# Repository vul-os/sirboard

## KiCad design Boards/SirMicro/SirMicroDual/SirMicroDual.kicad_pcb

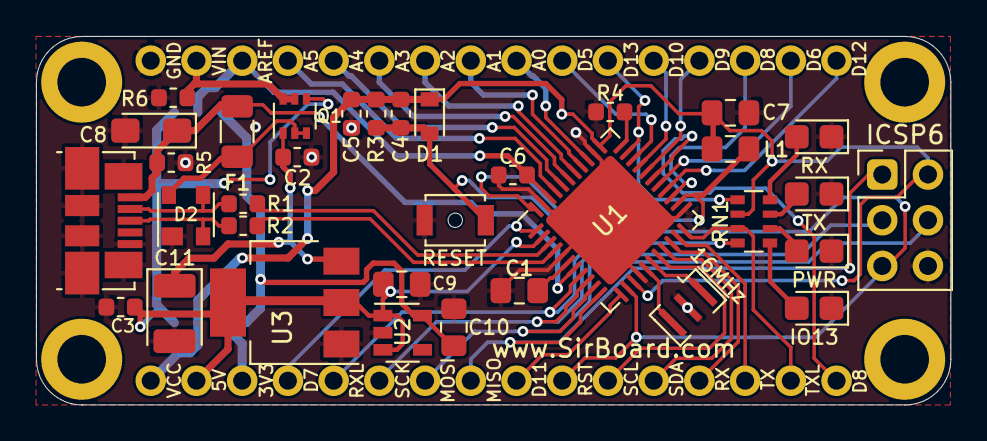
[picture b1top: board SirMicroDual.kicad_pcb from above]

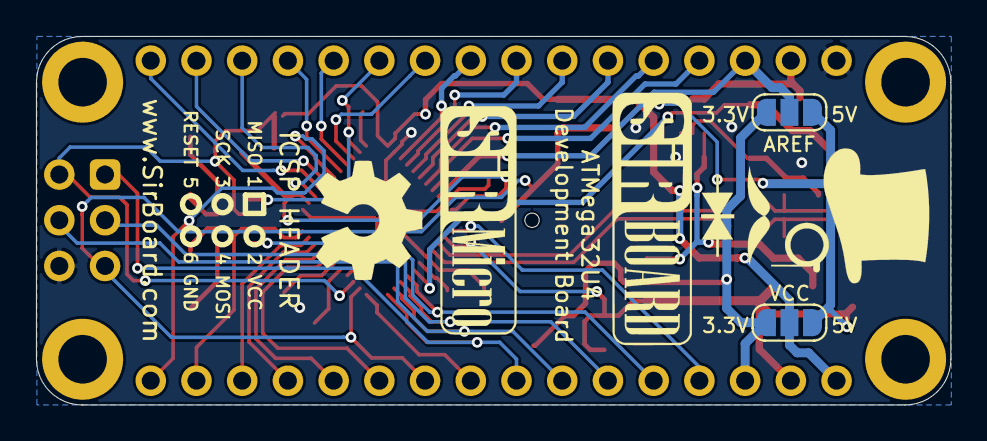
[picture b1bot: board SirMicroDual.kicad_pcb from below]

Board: 2 copper layers, 50.8 x 20.5 mm, 38 parts (4 on the bottom side), 48 nets.

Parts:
16MHz: 16MHz; Resonator_SMD_muRata_CSTxExxV-3Pin_3.0x1.1mm
C1, C7, C9, C10: 1uF; C_0805_2012Metric_Pad1.15x1.40mm_HandSolder
C2, C3, C4, C5, C6: 100nF; C_0603_1608Metric
C8: 22uF; CP_EIA-3216-18_Kemet-A_Pad1.58x1.35mm_HandSolder
C11: 22uF; CP_EIA-3528-12_Kemet-T
D1: D; D_SOD-110
D2: PRTR5V0U2X; SOT-143
F1: 500mA; R_1206_3216Metric
ICSP6: Conn_02x03_Odd_Even; PinHeader_2x03_P2.54mm_Vertical
IO13: LED; LED_0805_2012Metric_Castellated
J1, J2: Conn_01x16; PinHeader_1x16_P2.54mm_Vertical
J3: USB_B_Micro; USB_Micro-B_Molex_47346-0001
JP1, JP2: SolderJumper_3_Open; SolderJumper-3_P1.3mm_Open_RoundedPad1.0x1.5mm
L1: 10uH; L_0805_2012Metric_Pad1.15x1.40mm_HandSolder
PWR: LED; LED_0805_2012Metric_Castellated
Q1: DMP2004DWK-7; SOT-363_SC-70-6
R1, R2: 22e; R_0603_1608Metric
R3, R4, R5, R6: 10k; R_0603_1608Metric
RESET: SW_Push; SW_SPST_B3U-1000P-B
RN1: 1k; R_Array_Convex_4x0603
RX: LED; LED_0805_2012Metric_Castellated
TX: LED; LED_0805_2012Metric_Castellated
U1: ATmega32U4-MU; QFN-44-1EP_7x7mm_P0.5mm_EP5.2x5.2mm
U2: AP2127K-3.3; SOT-23-5
U3: AZ1117-5.0; SOT-223-3_TabPin2

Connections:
3V3: C10.1, J2.3, JP1.3, JP2.3, U2.5
5V: C3.1, C9.1, J2.2, JP1.1, JP2.1, Q1.4, U1.2, U2.1, U2.3, U3.2
/HWB: R4.1, U1.33
/X1: 16MHz.1, U1.17
/X2: 16MHz.3, U1.16
/uD+: R2.2, U1.4
/uD-: R1.2, U1.3
A0: J1.9, U1.36
A1: J1.8, U1.37
A2: J1.7, U1.38
A3: J1.6, U1.39
A4: J1.5, U1.40
A5: J1.4, U1.41
AREF: C6.1, J1.3, JP2.2, U1.42
D4: J1.14, U1.25
D5: J1.10, U1.31
D6: J1.15, U1.27
D7: J2.4, U1.1
D8: J2.16, U1.28
D9: J1.13, U1.29
D10: J1.12, U1.30
D11: J2.9, U1.12
D12: J1.16, U1.26
D13: J1.11, RN1.1, U1.32
D+: D2.2, J3.3, R2.1
D-: D2.3, J3.2, R1.1
GND: 16MHz.2, C1.2, C2.2, C3.2, C5.2, C6.2, C7.2, C8.2, C9.2, C10.2, C11.2, D2.1, ICSP6.6, IO13.1, J1.1, J3.5, J3.6, PWR.1, R4.2, R5.2, R6.2, RESET.1, RX.1, TX.1, U1.5, U1.15, U1.23, U1.35, U1.43, U1.45, U2.2, U3.1
MISO: ICSP6.1, J2.8, U1.11
MOSI: ICSP6.4, J2.7, U1.10
unnamed: C1.1, U1.6
unnamed: C8.1, F1.2, J3.1, R5.1, U1.7
unnamed: C2.1, C11.1, Q1.1, U3.3
unnamed: IO13.2, RN1.5
unnamed: L1.2, U1.24, U1.44
unnamed: PWR.2, RN1.6
unnamed: RN1.7, TX.2
unnamed: RN1.8, RX.2
RST: C4.2, D1.2, ICSP6.5, J2.10, R3.2, RESET.2, U1.13
RX: J2.13, U1.20
RXLED: J2.5, RN1.4, U1.8
SCK: ICSP6.3, J2.6, U1.9
SCL: J2.11, U1.18
SDA: J2.12, U1.19
TX: J2.14, U1.21
TXLED: J2.15, RN1.3, U1.22
VCC: C4.1, C5.1, C7.1, D1.1, ICSP6.2, J2.1, JP1.2, L1.1, R3.1, RN1.2, U1.14, U1.34
VIN: J1.2, Q1.5, Q1.6, R6.1
VUSB: D2.4, F1.1, Q1.2, Q1.3

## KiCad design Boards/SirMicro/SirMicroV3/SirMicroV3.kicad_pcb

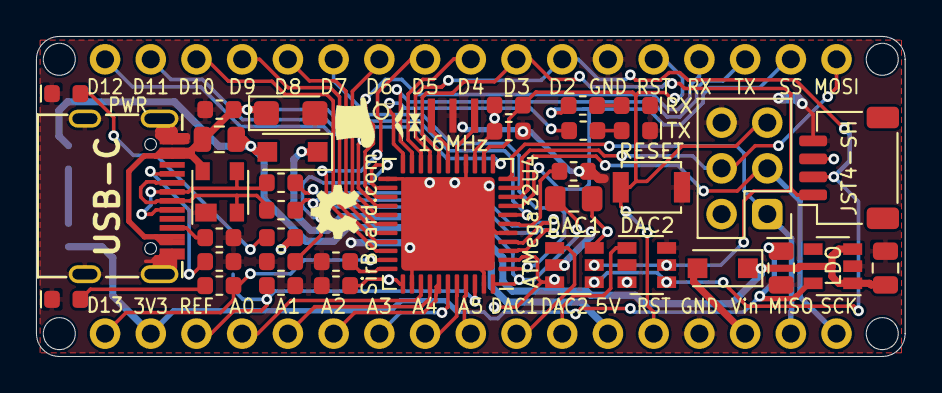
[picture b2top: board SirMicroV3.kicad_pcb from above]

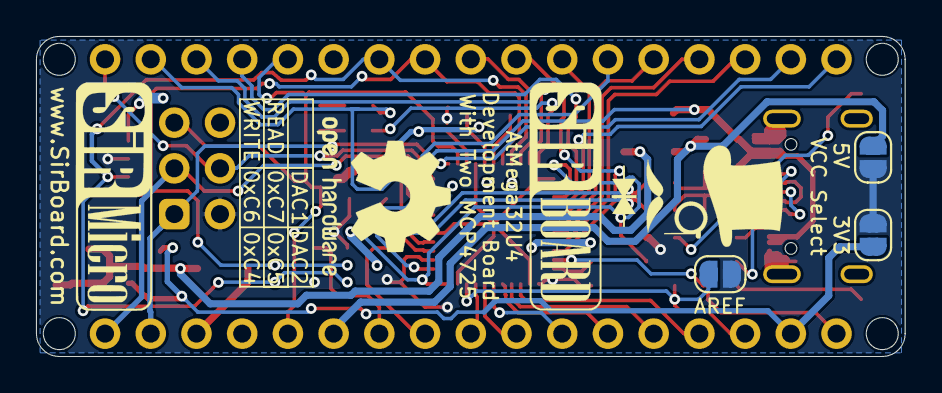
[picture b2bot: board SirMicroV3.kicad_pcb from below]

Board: 2 copper layers, 48.3 x 17.8 mm, 46 parts (5 on the bottom side), 51 nets.

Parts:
C1, C3, C4: 100nF; C_0603_1608Metric
C2, C9: 1uF; C_0603_1608Metric
C5, C7: 10uF; C_0805_2012Metric
C6: 10nF; C_0603_1608Metric
C8: 22uF; CP_EIA-3216-12_Kemet-S
D1: PRTR5V0U2X; SOT-143
D2, D3: MBR120; D_SOD-123F
D13: LED; LED_0603_1608Metric
DAC1, DAC2: MCP4725; SOT-23-6
F1: 500mA; R_0805_2012Metric
H1, H2, H3, H4: MountingHole; MountingHole_2.2mm_M2
J1, J2: Conn_01x17; PinHeader_1x17_P2.54mm_Vertical
J4: Conn_02x03_Odd_Even; PinHeader_2x03_P2.54mm_Vertical
JP1: AREF; SolderJumper-2_P1.3mm_Open_RoundedPad1.0x1.5mm
JP2, JP3: SolderJumper_2_Open; SolderJumper-2_P1.3mm_Open_RoundedPad1.0x1.5mm
JST4-SH: SirBlue; SirBlue_Connector
L1: 10uH; L_0805_2012Metric_Pad1.15x1.40mm_HandSolder
LDO: SPX3819M5-L-3-3; SOT-23-5
PWR: LED; LED_0603_1608Metric
R1, R2: 22e; R_0603_1608Metric
R3, R5: 10k; R_0603_1608Metric
R4, R8, R9, R10: 1k; R_0603_1608Metric
R11, R12: 5K1; R_0603_1608Metric
RESET: SW_Push; SW_SPST_B3U-1000P
RX: LED; LED_0603_1608Metric
TX: LED; LED_0603_1608Metric
U1: ATmega32U4-MU; QFN-44-1EP_7x7mm_P0.5mm_EP5.2x5.2mm
USB-C: USB_C_Plug_USB2.0; USB_C
Y1: 20MHz; Resonator_SMD_muRata_CSTxExxV-3Pin_3.0x1.1mm

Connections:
3V3: C7.1, J2.16, JP3.1, LDO.5
/D13LED: D13.2, R9.2
/HWB: R5.2, U1.33
/PWRLED: PWR.2, R10.2
/RXLED: R4.2, RX.2
/TXLED: R8.2, TX.2
/UCAP: C2.1, U1.6
/X1: U1.16, Y1.1
/X2: U1.17, Y1.3
A0: J2.14, U1.36
A1: J2.13, U1.37
A2: J2.12, U1.38
A3: J2.11, U1.39
A4: J2.10, U1.40
A5: J2.9, U1.41
AREF: C1.1, J2.15, JP1.2, U1.42
D4: J1.9, U1.20
D5: J1.10, U1.31
D6: J1.11, U1.27
D7: J1.12, U1.1
D8: J1.13, U1.28
D9: J1.14, U1.29
D10: J1.15, U1.30
D11: J1.16, U1.12
D12: J1.17, U1.26
D13: J2.17, R9.1, U1.32
D+: D1.3, R1.1, USB-C.A6, USB-C.B6
D-: D1.2, R2.1, USB-C.A7, USB-C.B7
GND: C1.2, C2.2, C3.2, C4.2, C5.2, C6.2, C7.2, C8.2, C9.2, D1.1, D13.1, DAC1.2, DAC2.2, DAC2.6, J1.6, J2.4, J4.6, JST4-SH.4, LDO.2, PWR.1, R5.1, R11.1, R12.1, RESET.2, RX.1, TX.1, U1.5, U1.15, U1.23, U1.35, U1.43, U1.45, USB-C.A1, USB-C.A12, USB-C.B1, USB-C.B12, USB-C.S1, Y1.2
MISO: J2.2, J4.1, U1.11
MOSI: J1.1, J4.4, U1.10
unnamed: C5.1, D2.1, D3.1, LDO.1, LDO.3
unnamed: C9.1, L1.2, U1.24, U1.44
unnamed: R12.2, USB-C.A5
unnamed: R11.2, USB-C.B5
RESET: J1.5, J2.5, J4.5, R3.2, RESET.1, U1.13
RX: J1.4, U1.25
RX_LED: J1.2, R4.1, U1.8
SCK: J2.1, J4.3, U1.9
SCL: DAC1.5, DAC2.5, J1.8, JST4-SH.1, U1.18
SDA: DAC1.4, DAC2.4, J1.7, JST4-SH.2, U1.19
TX: J1.3, U1.21
TX_LED: R8.1, U1.22
VBUS: C6.1, C8.1, D1.4, F1.2, U1.7, USB-C.A4, USB-C.A9, USB-C.B4, USB-C.B9
VCC: C3.1, C4.1, DAC1.3, DAC1.6, DAC2.3, J4.2, JP1.1, JP2.2, JP3.2, JST4-SH.3, L1.1, R3.1, R10.1, U1.2, U1.14, U1.34
VIN: D3.2, J2.3
VO1: DAC1.1, J2.8
VO2: DAC2.1, J2.7
VUSB: D2.2, F1.1, J2.6, JP2.1
uD+: R1.2, U1.4
uD-: R2.2, U1.3

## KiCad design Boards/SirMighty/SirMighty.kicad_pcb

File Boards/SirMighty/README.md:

# SirMighty
Microcontroller Development Board for the ATMega1284P which also works for the 644/324/32/16 derivatives. Fully Compatible with Arduino MightyCore

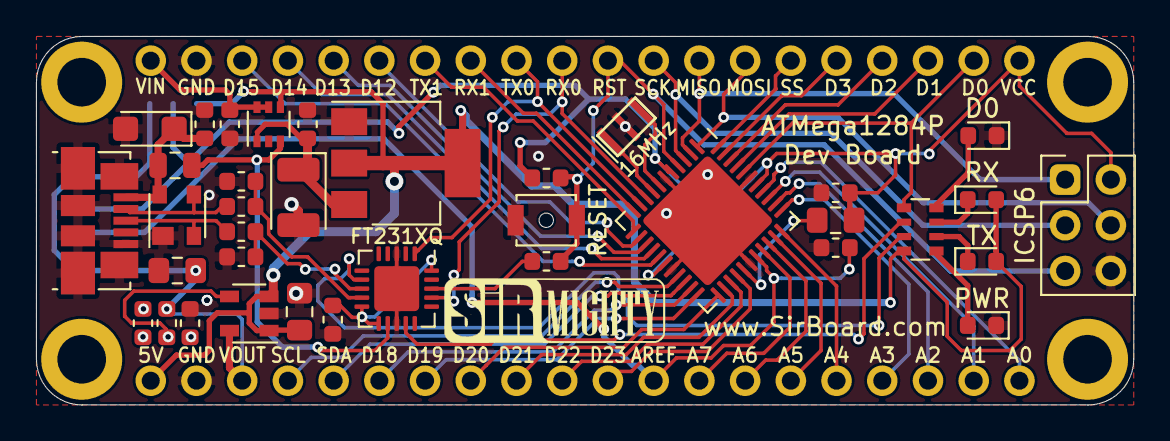
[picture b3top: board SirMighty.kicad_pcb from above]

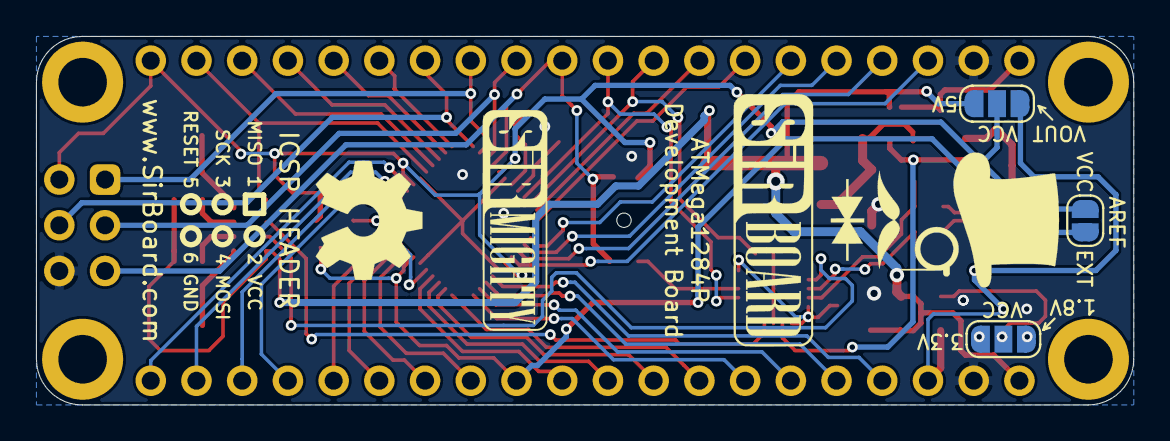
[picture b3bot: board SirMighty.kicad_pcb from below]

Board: 2 copper layers, 61.0 x 20.5 mm, 41 parts (5 on the bottom side), 60 nets.

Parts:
16MHz: 16MHz; Resonator_SMD_muRata_CSTxExxV-3Pin_3.0x1.1mm
C1, C5, C7, C11, C12: 100nF; C_0603_1608Metric
C2, C4: 47pF; C_0603_1608Metric
C3: 22uF; CP_EIA-3528-12_Kemet-T
C6: 10nF; C_0603_1608Metric
C8: 22uF; CP_EIA-3216-12_Kemet-S
C9, C10: 1uF; C_0805_2012Metric_Pad1.15x1.40mm_HandSolder
D0: LED; LED_0603_1608Metric
D1: PRTR5V0U2X; SOT-143
F1: 500mA; R_0805_2012Metric
FT231XQ: FT231XQ; QFN-20-1EP_4x4mm_P0.5mm_EP2.5x2.5mm
ICSP6: Conn_02x03_Odd_Even; PinHeader_2x03_P2.54mm_Vertical
J1, J2: Conn_01x20; PinHeader_1x20_P2.54mm_Vertical
J3: USB_B_Micro; USB_Micro-B_Molex_47346-0001
JP1: SolderJumper_2_Open; SolderJumper-2_P1.3mm_Open_RoundedPad1.0x1.5mm
JP2, JP3: SolderJumper_3_Open; SolderJumper-3_P1.3mm_Open_RoundedPad1.0x1.5mm
L1: 10uH; L_0805_2012Metric_Pad1.15x1.40mm_HandSolder
PWR: LED; LED_0603_1608Metric
Q1: Q_DUAL_PMOS_S1G1D2S2G2D1; SOT-363_SC-70-6
R1, R2: 27e; R_0603_1608Metric
R3, R4: 10k; R_0603_1608Metric
R5: 56k; R_0603_1608Metric
R6: 22k; R_0603_1608Metric
R7: 68k; R_0603_1608Metric
RESET: SW_Push; SW_SPST_B3U-1000P-B
RN1: 1k; R_Array_Convex_4x0603
RX: LED; LED_0603_1608Metric
TX: LED; LED_0603_1608Metric
U2: AP7365-W-7; SOT-23-5
U4: AZ1117-5.0; SOT-223-3_TabPin2
www.SirBoard.com: ATmega1284P-MU; QFN-44-1EP_7x7mm_P0.5mm_EP5.2x5.2mm

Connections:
3.3V: C12.2, FT231XQ.10, FT231XQ.11, FT231XQ.20
5V: C9.1, J1.1, JP3.3, Q1.4, RN1.4, RX.2, TX.2, U2.1, U2.3, U4.2
/D0LED: D0.2, RN1.8
/PWRLED: PWR.2, RN1.5
/X1: 16MHz.3, www.SirBoard.com.8
/X2: 16MHz.1, www.SirBoard.com.7
/uD+: C2.1, FT231XQ.8, R2.2
/uD-: C4.1, FT231XQ.9, R1.2
A0: J1.20, www.SirBoard.com.37
A1: J1.19, www.SirBoard.com.36
A2: J1.18, www.SirBoard.com.35
A3: J1.17, www.SirBoard.com.34
A4: J1.16, www.SirBoard.com.33
A5: J1.15, www.SirBoard.com.32
A6: J1.14, www.SirBoard.com.31
A7: J1.13, www.SirBoard.com.30
ADJ: JP2.2, R7.2, U2.4
AREF: C1.1, J1.12, JP1.1, www.SirBoard.com.29
D0: J2.19, RN1.1, www.SirBoard.com.40
D1: J2.18, www.SirBoard.com.41
D2: J2.17, www.SirBoard.com.42
D3: J2.16, www.SirBoard.com.43
D12: J2.6, www.SirBoard.com.13
D13: J2.5, www.SirBoard.com.14
D14: J2.4, www.SirBoard.com.15
D15: J2.3, www.SirBoard.com.16
D18: J1.6, www.SirBoard.com.21
D19: J1.7, www.SirBoard.com.22
D20: J1.8, www.SirBoard.com.23
D21: J1.9, www.SirBoard.com.24
D22: J1.10, www.SirBoard.com.25
D23: J1.11, www.SirBoard.com.26
D+: D1.2, J3.3, R2.1
D-: D1.3, J3.2, R1.1
GND: 16MHz.2, C1.2, C2.2, C3.2, C4.2, C5.2, C6.2, C7.2, C8.2, C9.2, C10.2, C12.1, D0.1, D1.1, FT231XQ.3, FT231XQ.13, FT231XQ.21, ICSP6.6, J1.2, J2.2, J3.5, J3.6, PWR.1, R4.2, R5.2, R6.2, RESET.2, U2.2, U4.1, www.SirBoard.com.6, www.SirBoard.com.18, www.SirBoard.com.28, www.SirBoard.com.39, www.SirBoard.com.45
MISO: ICSP6.1, J2.13, www.SirBoard.com.2
MOSI: ICSP6.4, J2.14, www.SirBoard.com.1
unnamed: C3.1, C5.1, Q1.1, U4.3
unnamed: C11.2, FT231XQ.18
unnamed: JP2.1, R6.1
unnamed: JP2.3, R5.1
unnamed: L1.2, www.SirBoard.com.27
unnamed: RN1.6, TX.1
unnamed: RN1.7, RX.1
RESET: C11.1, ICSP6.5, J2.11, R3.2, RESET.1, www.SirBoard.com.4
RXD0: FT231XQ.17, J2.10, www.SirBoard.com.9
RXD1: J2.8, www.SirBoard.com.11
RX_LED: FT231XQ.14, RN1.2
SCK: ICSP6.3, J2.12, www.SirBoard.com.3
SCL: J1.4, www.SirBoard.com.19
SDA: J1.5, www.SirBoard.com.20
SS: J2.15, www.SirBoard.com.44
TXD0: FT231XQ.1, J2.9, www.SirBoard.com.10
TXD1: J2.7, www.SirBoard.com.12
TX_LED: FT231XQ.7, RN1.3
VCC: C7.1, ICSP6.2, J2.20, JP1.2, JP3.2, L1.1, R3.1, www.SirBoard.com.5, www.SirBoard.com.17, www.SirBoard.com.38
VIN: J2.1, Q1.5, Q1.6, R4.1
VOUT: C10.1, J1.3, JP3.1, R7.1, U2.5
VUSB: F1.1, FT231XQ.12, Q1.2, Q1.3
Vbus: C6.1, C8.1, D1.4, F1.2, J3.1

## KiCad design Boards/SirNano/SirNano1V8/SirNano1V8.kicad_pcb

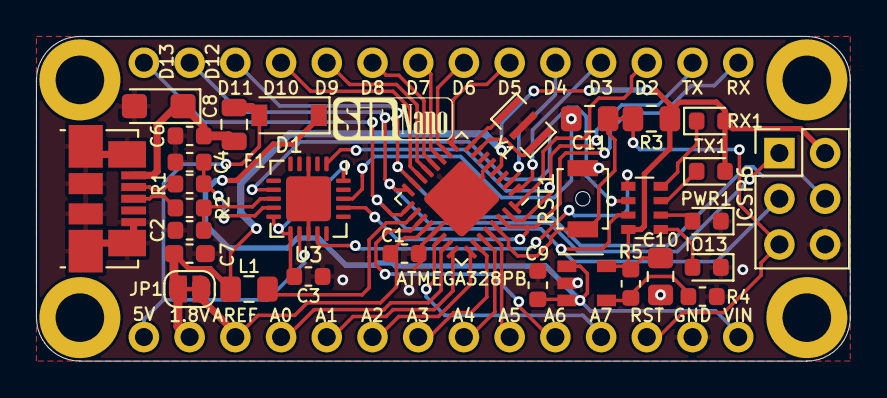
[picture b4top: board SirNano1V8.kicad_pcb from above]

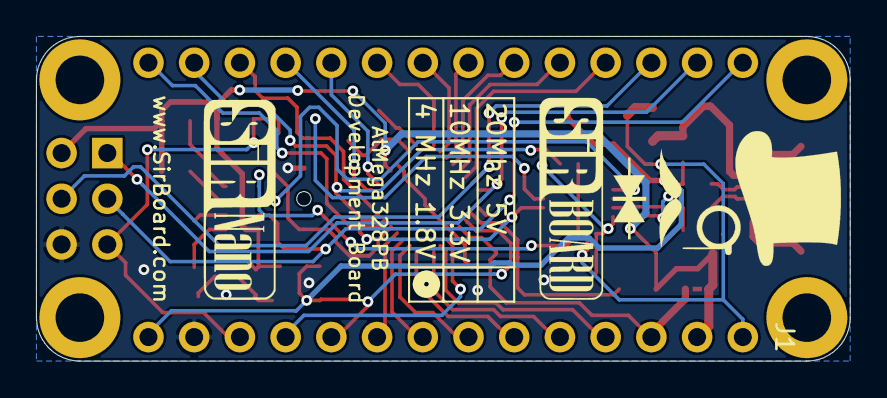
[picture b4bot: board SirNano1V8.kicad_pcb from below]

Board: 2 copper layers, 45.2 x 18.0 mm, 33 parts (2 on the bottom side), 45 nets.

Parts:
C1, C3: 100nF; C_0603_1608Metric
C2, C4: 47pF; C_0603_1608Metric
C6: 10nF; C_0603_1608Metric
C7: 1uF; C_0603_1608Metric_Pad1.05x0.95mm_HandSolder
C8: 22uF; CP_EIA-3216-12_Kemet-S
C9: 1uF; C_0603_1608Metric
C10: 2.2uF; C_0805_2012Metric_Pad1.15x1.40mm_HandSolder
C11: 100nF; C_0805_2012Metric_Pad1.15x1.40mm_HandSolder
D1: D_Schottky; D_SOD-123
F1: 500mA; R_0805_2012Metric
ICSP6: Conn_02x03_Odd_Even; PinHeader_2x03_P2.54mm_Vertical
IO13: LED; LED_0603_1608Metric
J1, J2: Conn_01x14; PinHeader_1x14_P2.54mm_Vertical
J3: USB_B_Micro; USB_Micro-B_Molex_47346-0001
JP1: SolderJumper_2_Bridged; SolderJumper-2_P1.3mm_Bridged_RoundedPad1.0x1.5mm
L1: 10uH; L_0805_2012Metric_Pad1.15x1.40mm_HandSolder
PWR1: LED; LED_0603_1608Metric
R1, R2: 27e; R_0603_1608Metric
R3: 10k; R_0805_2012Metric_Pad1.15x1.40mm_HandSolder
R4: 100k; R_0603_1608Metric
R5: 220k; R_0603_1608Metric
RN1: 1k; R_Array_Convex_4x0603
RST1: SW_Push; SW_SPST_B3U-1000P-B
RX1: LED; LED_0603_1608Metric
TX1: LED; LED_0603_1608Metric
U1: ATmega328PB-MU; QFN-32-1EP_5x5mm_P0.5mm_EP3.1x3.1mm
U2: AP2210K-ADJ; SOT-23-5
U3: FT231XQ; QFN-20-1EP_4x4mm_P0.5mm_EP2.5x2.5mm
Y1: 4MHz; Resonator_SMD_muRata_CSTxExxV-3Pin_3.0x1.1mm

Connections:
1V8: C7.1, C10.1, ICSP6.2, J1.2, JP1.2, L1.1, R3.1, R5.2, RN1.4, RX1.2, TX1.2, U1.4, U2.5
3V3: C3.1, U3.10, U3.11, U3.20
5V: D1.2, F1.1, J1.1, U3.12
/AREF: C1.1, J1.3, JP1.1, U1.20
/D2: J2.12, U1.32
/D3: J2.11, U1.1
/D4: J2.10, U1.2
/D5: J2.9, U1.9
/D6: J2.8, U1.10
/D7: J2.7, U1.11
/D8: J2.6, U1.12
/D9: J2.5, U1.13
/D10: J2.4, U1.14
/D+: J3.3, R2.1
/D-: J3.2, R1.1
/IO13LED: IO13.2, RN1.5
/PWRLED: PWR1.2, RN1.6
/RX: J2.14, U1.30, U3.17
/TX: J2.13, U1.31, U3.1
/X1: U1.7, Y1.3
/X2: U1.8, Y1.1
/uD+: C2.1, R2.2, U3.8
/uD-: C4.1, R1.2, U3.9
A0: J1.4, U1.23
A1: J1.5, U1.24
A2: J1.6, U1.25
A3: J1.7, U1.26
A4: J1.8, U1.27
A5: J1.9, U1.28
A6: J1.10, U1.19
A7: J1.11, U1.22
D11: ICSP6.4, J2.3, U1.15
D12: ICSP6.1, J2.2, U1.16
D13: ICSP6.3, J2.1, RN1.3, U1.17
GND: C1.2, C2.2, C3.2, C4.2, C6.2, C7.2, C8.2, C9.2, C10.2, ICSP6.6, IO13.1, J1.13, J3.5, J3.6, PWR1.1, R4.2, RST1.2, U1.5, U1.21, U1.33, U2.2, U3.3, U3.13, U3.21, Y1.2
unnamed: C6.1, C8.1, F1.2, J3.1
unnamed: C11.2, U3.18
unnamed: L1.2, U1.18
unnamed: R4.1, R5.1, U2.4
unnamed: RN1.7, TX1.1
unnamed: RN1.8, RX1.1
RESET: C11.1, ICSP6.5, J1.12, R3.2, RST1.1, U1.29
RX_LED: RN1.1, U3.14
TX_LED: RN1.2, U3.7
VIN: C9.1, D1.1, J1.14, U2.1, U2.3

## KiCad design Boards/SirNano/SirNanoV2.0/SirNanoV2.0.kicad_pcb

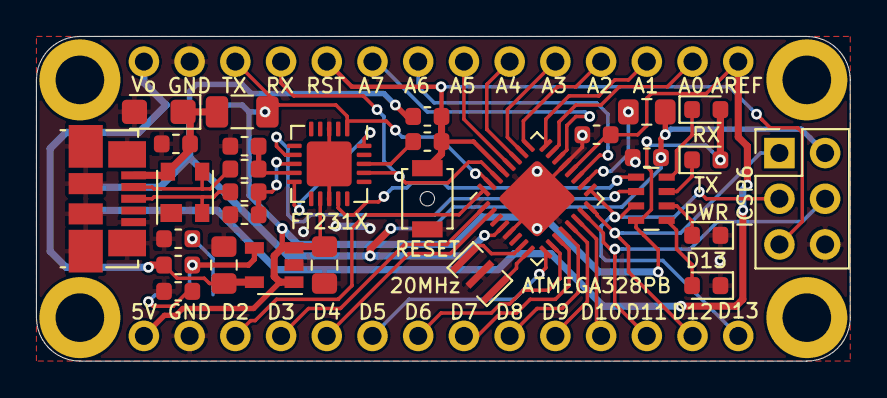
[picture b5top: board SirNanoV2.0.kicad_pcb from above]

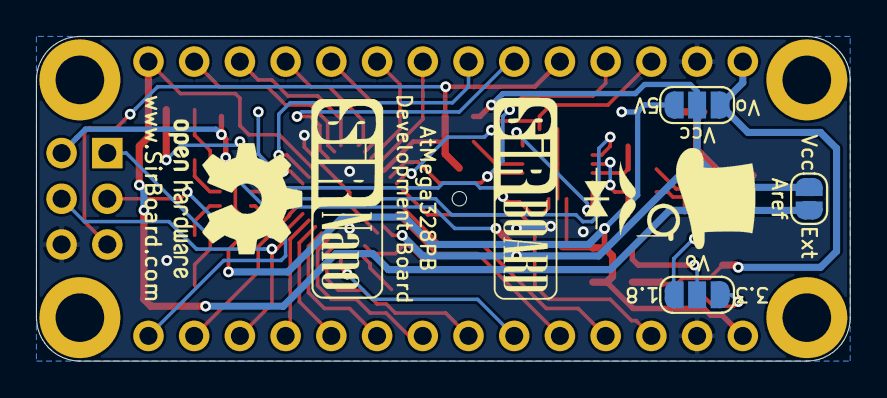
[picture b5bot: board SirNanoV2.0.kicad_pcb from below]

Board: 2 copper layers, 45.2 x 18.0 mm, 35 parts (5 on the bottom side), 47 nets.

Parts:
20MHz: 20MHz; Resonator_SMD_muRata_CSTxExxV-3Pin_3.0x1.1mm
C1, C11: 100nF; C_0603_1608Metric
C2, C4: 47pF; C_0603_1608Metric
C6: 10nF; C_0603_1608Metric
C7: 1uF; C_0603_1608Metric
C8: 22uF; CP_EIA-3216-12_Kemet-S
C9, C10: 1uF; C_0805_2012Metric_Pad1.15x1.40mm_HandSolder
D1: PRTR5V0U2X; SOT-143
D13: LED; LED_0603_1608Metric
F1: 500mA; R_1206_3216Metric
FT231X: FT231XQ; QFN-20-1EP_4x4mm_P0.5mm_EP2.5x2.5mm
ICSP6: Conn_02x03_Odd_Even; PinHeader_2x03_P2.54mm_Vertical
J1, J2: Conn_01x14; PinHeader_1x14_P2.54mm_Vertical
J3: USB_B_Micro; USB_Micro-B_Molex_47346-0001
JP1: SolderJumper_2_Bridged; SolderJumper-2_P1.3mm_Open_RoundedPad1.0x1.5mm
JP2, JP3: SolderJumper_3_Open; SolderJumper-3_P1.3mm_Open_RoundedPad1.0x1.5mm
L1: 10uH; L_0805_2012Metric_Pad1.15x1.40mm_HandSolder
PWR: LED; LED_0603_1608Metric
R1, R2: 27e; R_0603_1608Metric
R3: 10k; R_0603_1608Metric
R5: 56k; R_0603_1608Metric
R6: 22k; R_0603_1608Metric
R7: 68k; R_0603_1608Metric
RESET: SW_Push; SW_SPST_B3U-1000P-B
RN1: R_Pack04; R_Array_Concave_4x0603
RX: LED; LED_0603_1608Metric
TX: LED; LED_0603_1608Metric
U1: ATmega328PB-MU; QFN-32-1EP_5x5mm_P0.5mm_EP3.1x3.1mm
U2: AP7365-ADJ; SOT-23-5

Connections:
1.8V: JP2.3, R5.1
3.3V: FT231X.10, FT231X.20
3_3V: JP2.1, R6.1
5V: C9.1, F1.1, FT231X.12, J1.1, JP3.3, RN1.4, RX.2, TX.2, U2.1, U2.3
/IO13LED: D13.2, RN1.5
/PWRLED: PWR.2, RN1.6
/X1: 20MHz.3, U1.7
/X2: 20MHz.1, U1.8
/uD+: C2.1, FT231X.8, R2.2
/uD-: C4.1, FT231X.9, R1.2
A0: J2.13, U1.23
A1: J2.12, U1.24
A2: J2.11, U1.25
A3: J2.10, U1.26
A4: J2.9, U1.27
A5: J2.8, U1.28
A6: J2.7, U1.19
A7: J2.6, U1.22
ADJ: JP2.2, R7.2, U2.4
AREF: C1.1, J2.14, JP1.1, U1.20
D2: J1.3, U1.32
D3: J1.4, U1.1
D4: J1.5, U1.2
D5: J1.6, U1.9
D6: J1.7, U1.10
D7: J1.8, U1.11
D8: J1.9, U1.12
D9: J1.10, U1.13
D10: J1.11, U1.14
D11: ICSP6.4, J1.12, U1.15
D12: ICSP6.1, J1.13, U1.16
D13: ICSP6.3, J1.14, RN1.3, U1.17
D+: D1.2, J3.3, R2.1
D-: D1.3, J3.2, R1.1
GND: 20MHz.2, C1.2, C2.2, C4.2, C6.2, C7.2, C8.2, C9.2, C10.2, D1.1, D13.1, FT231X.3, FT231X.13, FT231X.21, ICSP6.6, J1.2, J2.2, J3.5, J3.6, PWR.1, R5.2, R6.2, RESET.2, U1.5, U1.21, U1.33, U2.2
unnamed: C11.2, FT231X.18
unnamed: L1.2, U1.18
unnamed: RN1.7, TX.1
unnamed: RN1.8, RX.1
RESET: C11.1, ICSP6.5, J2.5, R3.2, RESET.1, U1.29
RX: FT231X.17, J2.4, U1.30
RX_LED: FT231X.14, RN1.1
TX: FT231X.1, J2.3, U1.31
TX_LED: FT231X.7, RN1.2
VBUS: C6.1, C8.1, D1.4, F1.2, J3.1
VCC: C7.1, ICSP6.2, JP1.2, JP3.2, L1.1, R3.1, U1.4
VOUT: C10.1, J2.1, JP3.1, R7.1, U2.5

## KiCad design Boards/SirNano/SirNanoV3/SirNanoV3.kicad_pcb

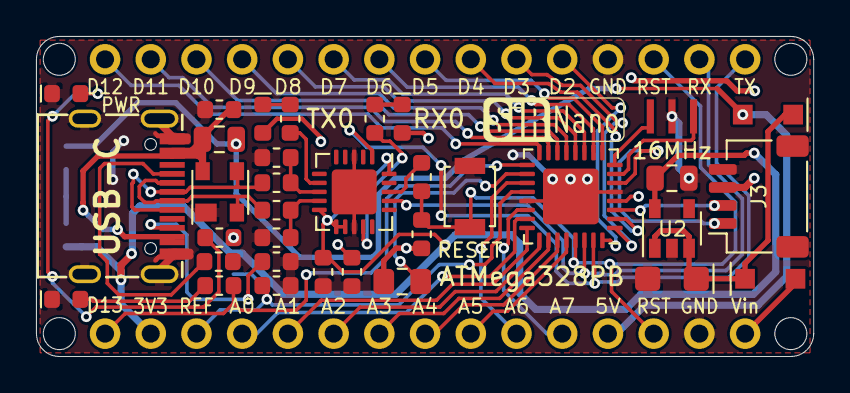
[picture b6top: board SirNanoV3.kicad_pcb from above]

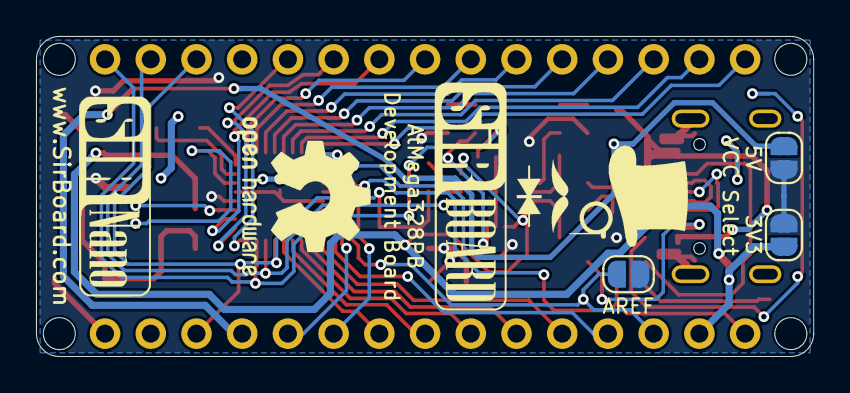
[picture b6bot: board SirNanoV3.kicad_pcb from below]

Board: 2 copper layers, 43.2 x 17.8 mm, 43 parts (5 on the bottom side), 49 nets.

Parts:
C1, C3, C9, C11: 100nF; C_0603_1608Metric
C2, C4: 47pF; C_0603_1608Metric
C6: 10nF; C_0603_1608Metric
C7: 10uF; C_0805_2012Metric
C8: 22uF; CP_EIA-3216-12_Kemet-S
D1: PRTR5V0U2X; SOT-143
D2, D3: MBR120; D_SOD-123F
D13: LED; LED_0603_1608Metric
F1: 500mA; R_0805_2012Metric
H1, H2, H3, H4: MountingHole; MountingHole_2.2mm_M2
J1, J2: Conn_01x15; PinHeader_1x15_P2.54mm_Vertical
J3: SirBlue; SirBlue_Connector
JP1, JP2, JP3: AREF; SolderJumper-2_P1.3mm_Open_RoundedPad1.0x1.5mm
L1: 10uH; L_0805_2012Metric_Pad1.15x1.40mm_HandSolder
PWR: LED; LED_0603_1608Metric
R1, R2: 27e; R_0603_1608Metric
R3: 10k; R_0603_1608Metric
R4, R8, R9, R10: 1k; R_0603_1608Metric
R11, R12: 5K1; R_0603_1608Metric
RESET: SW_Push; SW_SPST_B3U-1000P
RX0: LED; LED_0603_1608Metric
TX0: LED; LED_0603_1608Metric
U1: ATmega328PB-MU; QFN-32-1EP_5x5mm_P0.5mm_EP3.1x3.1mm
U2: SPX3819M5-L-3-3; SOT-23-5
U3: FT231XQ; QFN-20-1EP_4x4mm_P0.5mm_EP2.5x2.5mm
USB-C: USB_C_Plug_USB2.0; USB_C
Y1: 16MHz; Resonator_SMD_muRata_CSTxExxV-3Pin_3.0x1.1mm

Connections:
3V3: C3.1, C7.1, J2.14, JP3.1, U2.5, U3.10, U3.11, U3.12, U3.20
/D13LED: D13.2, R9.2
/LDO_in: C8.1, D2.1, D3.1, U2.1, U2.3
/PWRLED: PWR.2, R10.2
/RXLED: R4.2, RX0.1
/TXLED: R8.2, TX0.1
/X1: U1.7, Y1.3
/X2: U1.8, Y1.1
/uD+: C2.1, R1.2, U3.8
/uD-: C4.1, R2.2, U3.9
A0: J2.12, U1.23
A1: J2.11, U1.24
A2: J2.10, U1.25
A3: J2.9, U1.26
A4: J2.8, U1.27
A5: J2.7, U1.28
A6: J2.6, U1.19
A7: J2.5, U1.22
AREF: C1.1, J2.13, JP1.1, U1.20
D2: J1.11, U1.32
D3: J1.10, U1.1
D4: J1.9, U1.2
D5: J1.8, U1.9
D6: J1.7, U1.10
D7: J1.6, U1.11
D8: J1.5, U1.12
D9: J1.4, U1.13
D10: J1.3, U1.14
D11: J1.2, U1.15
D12: J1.1, U1.16
D13: J2.15, R9.1, U1.17
D+: D1.3, R1.1, USB-C.A6, USB-C.B6
D-: D1.2, R2.1, USB-C.A7, USB-C.B7
GND: C1.2, C2.2, C3.2, C4.2, C6.2, C7.2, C8.2, C9.2, D1.1, D13.1, J1.12, J2.2, J3.4, PWR.1, R11.1, R12.1, RESET.2, U1.5, U1.21, U1.33, U2.2, U3.3, U3.13, U3.21, USB-C.A1, USB-C.A12, USB-C.B1, USB-C.B12, USB-C.S1, Y1.2
unnamed: C11.2, U3.18
unnamed: L1.2, U1.18
unnamed: R12.2, USB-C.A5
unnamed: R11.2, USB-C.B5
RESET: C11.1, J1.13, J2.3, R3.2, RESET.1, U1.29
RX: J1.14, U1.30, U3.17
RX_LED: R4.1, U3.14
SCL1: J3.1, U1.6
SDA1: J3.2, U1.3
TX: J1.15, U1.31, U3.1
TX_LED: R8.1, U3.7
VBUS: C6.1, D1.4, F1.2, USB-C.A4, USB-C.A9, USB-C.B4, USB-C.B9
VCC: C9.1, J3.3, JP1.2, JP2.2, JP3.2, L1.1, R3.1, R10.1, RX0.2, TX0.2, U1.4
VIN: D3.2, J2.1
VUSB: D2.2, F1.1, J2.4, JP2.1
